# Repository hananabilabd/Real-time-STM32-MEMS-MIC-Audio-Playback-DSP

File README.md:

# STM32F446RC Audio Playback using MEMS Microphone & I2S for Audio acquisition and DAC for Playback
MEMS microphone --> I2S --> **STM32F446RC** -->PDM to PCM --> DAC --> Speaker

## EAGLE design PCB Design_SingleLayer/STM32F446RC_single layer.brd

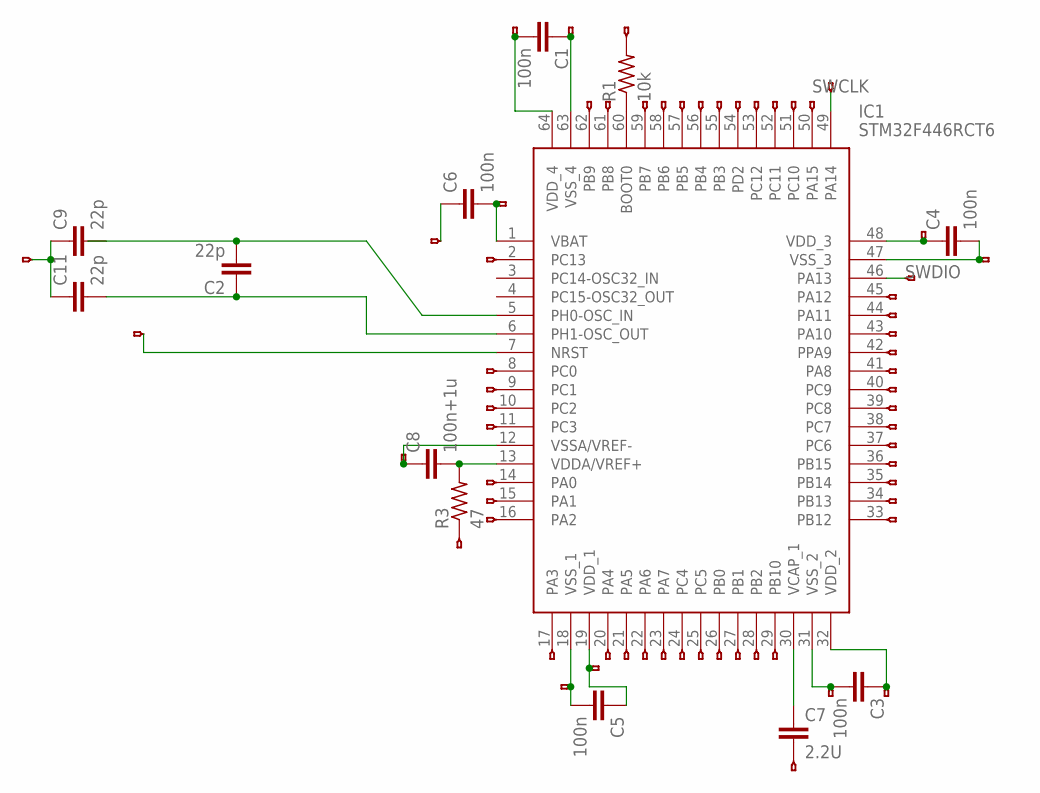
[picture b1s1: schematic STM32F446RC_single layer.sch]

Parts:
C1, C3, C4, C5, C6: 100n; C2.5-3
C2, C9, C11: 22p; C2.5-3
C7: 2.2U; C2.5-3
C8: 100n+1u; C2.5-3
IC1: STM32F446RCT6; QFP50P1200X1200X160-64N
JP1, JP2, JP3, JP4, JP5, JP6, JP7, JP9, JP10, JP11, JP12, JP13, JP14, JP15, JP16, JP17, JP18, JP19, JP20, JP21, JP22, JP23, JP24, JP25, JP26, JP27, JP28, JP29, JP30, JP31, JP32, JP33, JP34, JP35, JP36, JP37, JP38, JP39, JP40, JP41, JP42, JP43, JP44, JP45, JP46, JP47, JP48, JP49, JP50, JP51, JP52, JP53, JP54, JP55, JP56, JP57, JP58, JP59, JP61, JP62, JP63, JP65: HEADERHOLE-HEADERHOLE; 1X1-HEADER-HOLE
R1: 10k; 0204V
R3: 47; 0204V

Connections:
unnamed: C3.2, IC1.31 (VSS_2), JP50.1
unnamed: C8.2, IC1.13 (VDDA/VREF+), R3.2
unnamed: IC1.7 (NRST), JP63.1
unnamed: C5.2, IC1.18 (VSS_1), JP20.1
unnamed: IC1.60 (BOOT0), R1.1
unnamed: C1.2, IC1.64 (VDD_4), JP58.1
unnamed: C2.1, C11.2, IC1.6 (PH1-OSC_OUT)
unnamed: C1.1, IC1.63 (VSS_4), JP57.1
unnamed: IC1.59 (PB7), JP43.1
unnamed: IC1.58 (PB6), JP42.1
unnamed: IC1.24 (PC4), JP12.1
unnamed: IC1.25 (PC5), JP23.1
unnamed: IC1.26 (PB0), JP22.1
unnamed: IC1.27 (PB1), JP17.1
unnamed: IC1.28 (PB2), JP16.1
unnamed: IC1.29 (PB10), JP14.1
unnamed: IC1.23 (PA7), JP11.1
unnamed: IC1.22 (PA6), JP9.1
unnamed: IC1.21 (PA5), JP19.1
unnamed: IC1.17 (PA3), JP24.1
unnamed: IC1.33 (PB12), JP18.1
unnamed: IC1.34 (PB13), JP13.1
unnamed: IC1.35 (PB14), JP6.1
unnamed: IC1.36 (PB15), JP10.1
unnamed: IC1.37 (PC6), JP1.1
unnamed: IC1.16 (PA2), JP36.1
unnamed: IC1.15 (PA1), JP35.1
unnamed: IC1.14 (PA0), JP34.1
unnamed: IC1.11 (PC3), JP4.1
unnamed: IC1.10 (PC2), JP3.1
unnamed: IC1.9 (PC1), JP27.1
unnamed: IC1.8 (PC0), JP29.1
unnamed: IC1.2 (PC13), JP26.1
unnamed: IC1.38 (PC7), JP15.1
unnamed: IC1.39 (PC8), JP2.1
unnamed: IC1.40 (PC9), JP30.1
unnamed: IC1.41 (PA8), JP28.1
unnamed: IC1.42 (PPA9), JP31.1
unnamed: IC1.43 (PA10), JP33.1
unnamed: IC1.44 (PA11), JP32.1
unnamed: IC1.45 (PA12), JP25.1
unnamed: IC1.57 (PB5), JP41.1
unnamed: IC1.56 (PB4), JP40.1
unnamed: IC1.55 (PB3), JP44.1
unnamed: IC1.54 (PD2), JP38.1
unnamed: IC1.53 (PC12), JP39.1
unnamed: IC1.52 (PC11), JP5.1
unnamed: IC1.51 (PC10), JP37.1
unnamed: IC1.50 (PA15), JP45.1
unnamed: IC1.61 (PB8), JP46.1
unnamed: IC1.62 (PB9), JP47.1
unnamed: IC1.20 (PA4), JP21.1
unnamed: C2.2, IC1.5 (PH0-OSC_IN)
unnamed: C7.2, JP49.1
unnamed: C3.1, IC1.32 (VDD_2), JP51.1
unnamed: C4.2, IC1.47 (VSS_3), JP52.1
unnamed: JP56.1, R1.2
unnamed: C6.2, IC1.1 (VBAT), JP7.1
unnamed: C8.1, IC1.12 (VSSA/VREF-), JP62.1
unnamed: JP61.1, R3.1
unnamed: C9.1, C11.1, JP65.1
unnamed: C5.1, IC1.19 (VDD_1), JP48.1
unnamed: C7.1, IC1.30 (VCAP_1)
unnamed: C6.1, JP59.1
unnamed: C4.1, IC1.48 (VDD_3), JP53.1
SWCLK: IC1.49 (PA14), JP55.1
SWDIO: IC1.46 (PA13), JP54.1

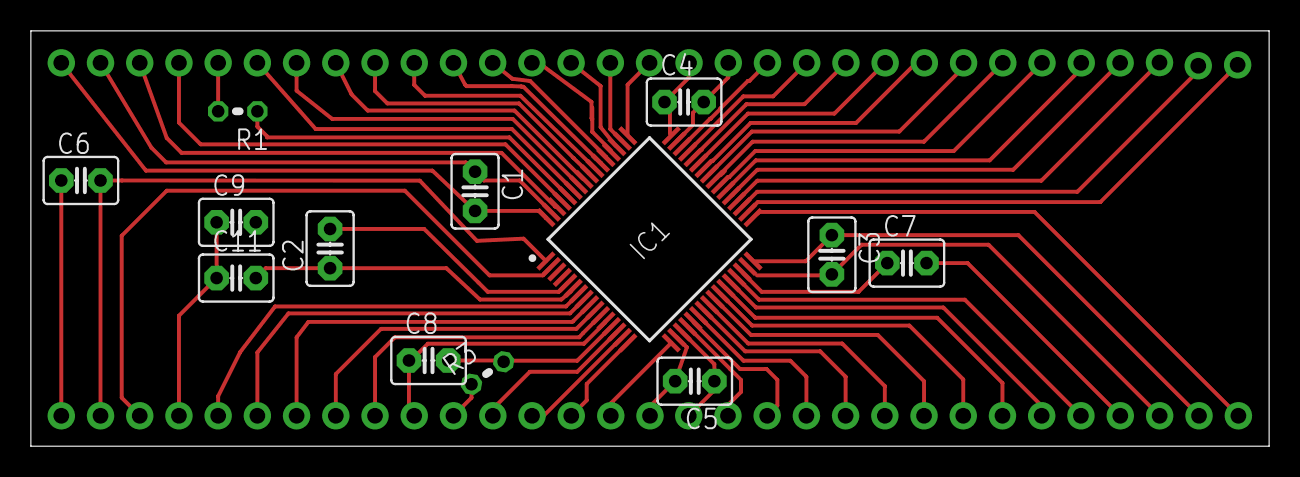
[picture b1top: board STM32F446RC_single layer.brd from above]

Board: 2 copper layers, 80.2 x 26.9 mm, 75 parts (0 on the bottom side), 67 nets.

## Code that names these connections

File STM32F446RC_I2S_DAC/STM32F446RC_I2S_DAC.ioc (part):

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Mcu.Name=STM32F446R(C-E)Tx
Mcu.Package=LQFP64
Mcu.UserName=STM32F446RCTx
PA0-WKUP.Mode=Asynchronous
PA0-WKUP.Signal=UART4_TX
PA1.Mode=Asynchronous
PA1.Signal=UART4_RX
PA13.Mode=Serial_Wire
PA13.Signal=SYS_JTMS-SWDIO
PA14.Mode=Serial_Wire
PA14.Signal=SYS_JTCK-SWCLK
PA15.Mode=Half_Duplex_Master
PA15.Signal=I2S3_WS
PA4.Signal=COMP_DAC1_group
PB1.GPIOParameters=PinState
PB1.PinState=GPIO_PIN_SET
PB1.Signal=GPIO_Output
PB12.Mode=Half_Duplex_Master
PB12.Signal=I2S2_WS
PB13.Mode=Half_Duplex_Master
PB13.Signal=I2S2_CK
PB6.Mode=I2C
PB6.Signal=I2C1_SCL
PB7.Mode=I2C
PB7.Signal=I2C1_SDA
PC1.Mode=Half_Duplex_Master
PC1.Signal=I2S3_SD
PC10.Mode=Half_Duplex_Master
PC10.Signal=I2S3_CK
PC3.Mode=Half_Duplex_Master
PC3.Signal=I2S2_SD
PC4.Signal=GPIO_Output
PC7.Mode=Master_Clock_Activated
PC7.Signal=I2S3_MCK
PH0-OSC_IN.Mode=HSE-External-Oscillator
PH0-OSC_IN.Signal=RCC_OSC_IN
PH1-OSC_OUT.Mode=HSE-External-Oscillator
PH1-OSC_OUT.Signal=RCC_OSC_OUT
RCC.HSE_VALUE=8000000
RCC.SYSCLKFreq_VALUE=100000000
RCC.SYSCLKSource=RCC_SYSCLKSOURCE_PLLCLK
board=custom

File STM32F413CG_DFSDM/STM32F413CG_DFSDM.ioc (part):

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Mcu.Name=STM32F413C(G-H)Ux
Mcu.Package=UFQFPN48
Mcu.UserName=STM32F413CGUx
PA15.Mode=Half_Duplex_Master
PA15.Signal=I2S3_WS
PA4.Signal=S_DATAIN1DFSDM1
PA5.GPIOParameters=PinState
PA5.PinState=GPIO_PIN_SET
PA5.Signal=GPIO_Output
PA8.Signal=S_CKOUTDFSDM1
PB10.Mode=Master_Clock_Activated
PB10.Signal=I2S3_MCK
PB3.Mode=Half_Duplex_Master
PB3.Signal=I2S3_CK
PB5.Mode=Half_Duplex_Master
PB5.Signal=I2S3_SD
PB6.Mode=I2C
PB6.Signal=I2C1_SCL
PB7.Mode=I2C
PB7.Signal=I2C1_SDA
PB8.GPIOParameters=GPIO_Speed,PinState
PB8.GPIO_Speed=GPIO_SPEED_FREQ_MEDIUM
PB8.PinState=GPIO_PIN_SET
PB8.Signal=GPIO_Output
PH0\ -\ OSC_IN.Mode=HSE-External-Oscillator
PH0\ -\ OSC_IN.Signal=RCC_OSC_IN
PH1\ -\ OSC_OUT.Mode=HSE-External-Oscillator
PH1\ -\ OSC_OUT.Signal=RCC_OSC_OUT
RCC.HSE_VALUE=8000000
RCC.SYSCLKFreq_VALUE=80000000
RCC.SYSCLKSource=RCC_SYSCLKSOURCE_PLLCLK
board=custom

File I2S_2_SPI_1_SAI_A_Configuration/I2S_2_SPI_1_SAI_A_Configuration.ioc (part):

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Mcu.Name=STM32F446R(C-E)Tx
Mcu.Package=LQFP64
Mcu.UserName=STM32F446RCTx
PA3.Mode=SAI_A_Master
PA3.Signal=SAI1_FS_A
PA5.Mode=RX_Only_Simplex_Unidirect_Master
PA5.Signal=SPI1_SCK
PA6.Mode=RX_Only_Simplex_Unidirect_Master
PA6.Signal=SPI1_MISO
PB10.Mode=SAI_A_Master
PB10.Signal=SAI1_SCK_A
PB12.Mode=Half_Duplex_Master
PB12.Signal=I2S2_WS
PB13.Mode=Half_Duplex_Master
PB13.Signal=I2S2_CK
PC1.Mode=SAI_A_Master
PC1.Signal=SAI1_SD_A
PC3.Mode=Half_Duplex_Master
PC3.Signal=I2S2_SD
PH0-OSC_IN.Mode=HSE-External-Oscillator
PH0-OSC_IN.Signal=RCC_OSC_IN
PH1-OSC_OUT.Mode=HSE-External-Oscillator
PH1-OSC_OUT.Signal=RCC_OSC_OUT
RCC.HSE_VALUE=8000000
RCC.SYSCLKFreq_VALUE=65523809.52380953
RCC.SYSCLKSource=RCC_SYSCLKSOURCE_PLLCLK
board=custom

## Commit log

2019-04-13 intial
2019-04-17 added pcb design of the single layer
2019-04-17 Adding CRC to the project to use in PDM2PCM conversion.
2019-04-17 Initialize PDM Filter structure
2019-04-19 Add #include "pdm2pcm_glo.h"
2019-04-19 Import "I2S_Configuration" project which generated from STM32CubeMX to an eclipse project under Eclipse folder with name "GP_Test_1"
2019-04-22 added schematic photo
2019-05-04 added test project
2019-05-06 adding int the main.c
2019-05-06 configure HSE to be 16 MHZ instead of 8 MHZ
2019-05-06 modify in main.c
2019-05-06 Added dac
2019-05-07 added
2019-05-08 first working!!!
2019-05-08 added first working!!!
2019-05-09 resemble Example version
2019-05-09 first working !!!
2019-05-09 added python real time python visualization
2019-05-21 edited .gitignore to upload debug folder content
2019-05-21 removed I2S_configuration_2 project
2019-06-13 final edit so far in I2S_3
2019-06-15 added my files
2019-06-19 added final touch
2019-06-19 final touch2
2019-06-19 added gitignore
2019-06-19 added after gitIgnore refresh
2019-06-19 after GitIgnore refresh - after deleting cache
2019-06-19 Configure I2C_1 and I2S_3 to use them to connect to CS43L22 audio codec IC
2019-06-20 Initial version of Documentation.
2019-06-20 added documentation folder
2019-06-20 initial version of documentations
2019-06-20 documentation about audio codec CS43L22 added
2019-06-20 Documentation about PDM2PCM library added.
2019-06-21 initial version of description part added to the documentation.
2019-06-22 ADDED DFSDM project
2019-06-23 Initial version of the presentation.
2019-06-23 Block Diagram added to the presentation.
2019-06-23 Add details to Documentation and Presentation.
2019-06-23 Add more details in Documentation and Presentation.
2019-06-25 Added details in the Documentation.
2019-06-25 add Documentation.pdf
2019-06-25 added parametricEqualizer
2019-06-26 nothing
2019-06-26 Add UART to receive data from bluetooth module
2019-06-26 finalizing
2020-02-22 added latest
2020-04-24 cleaning Repo
2020-04-24 cleaning Repo2
